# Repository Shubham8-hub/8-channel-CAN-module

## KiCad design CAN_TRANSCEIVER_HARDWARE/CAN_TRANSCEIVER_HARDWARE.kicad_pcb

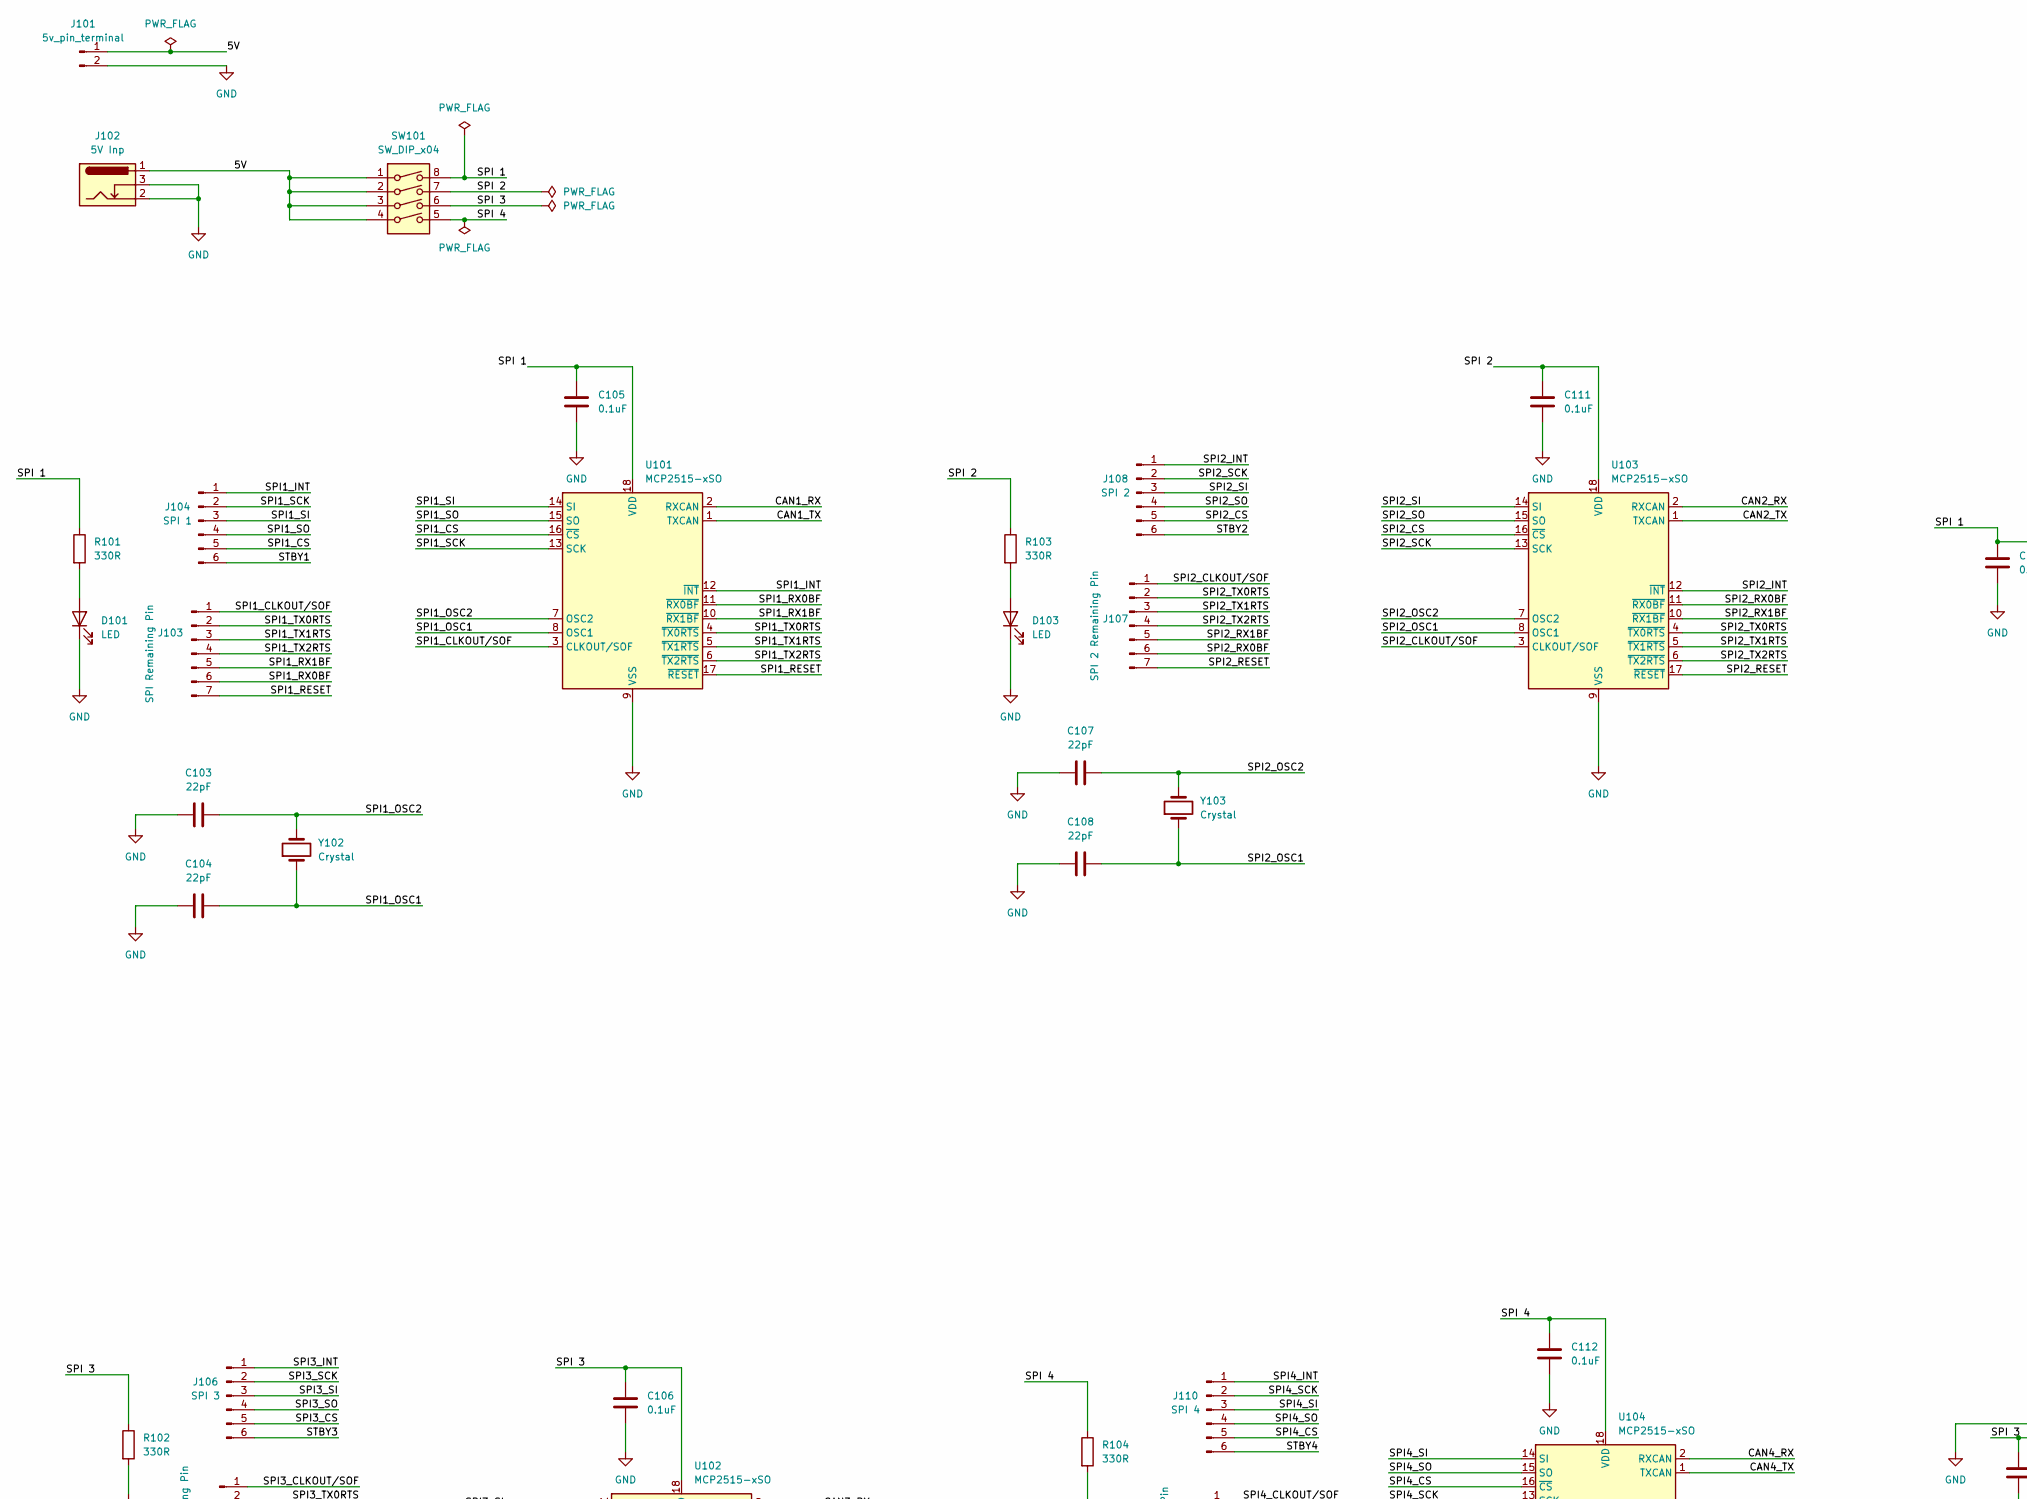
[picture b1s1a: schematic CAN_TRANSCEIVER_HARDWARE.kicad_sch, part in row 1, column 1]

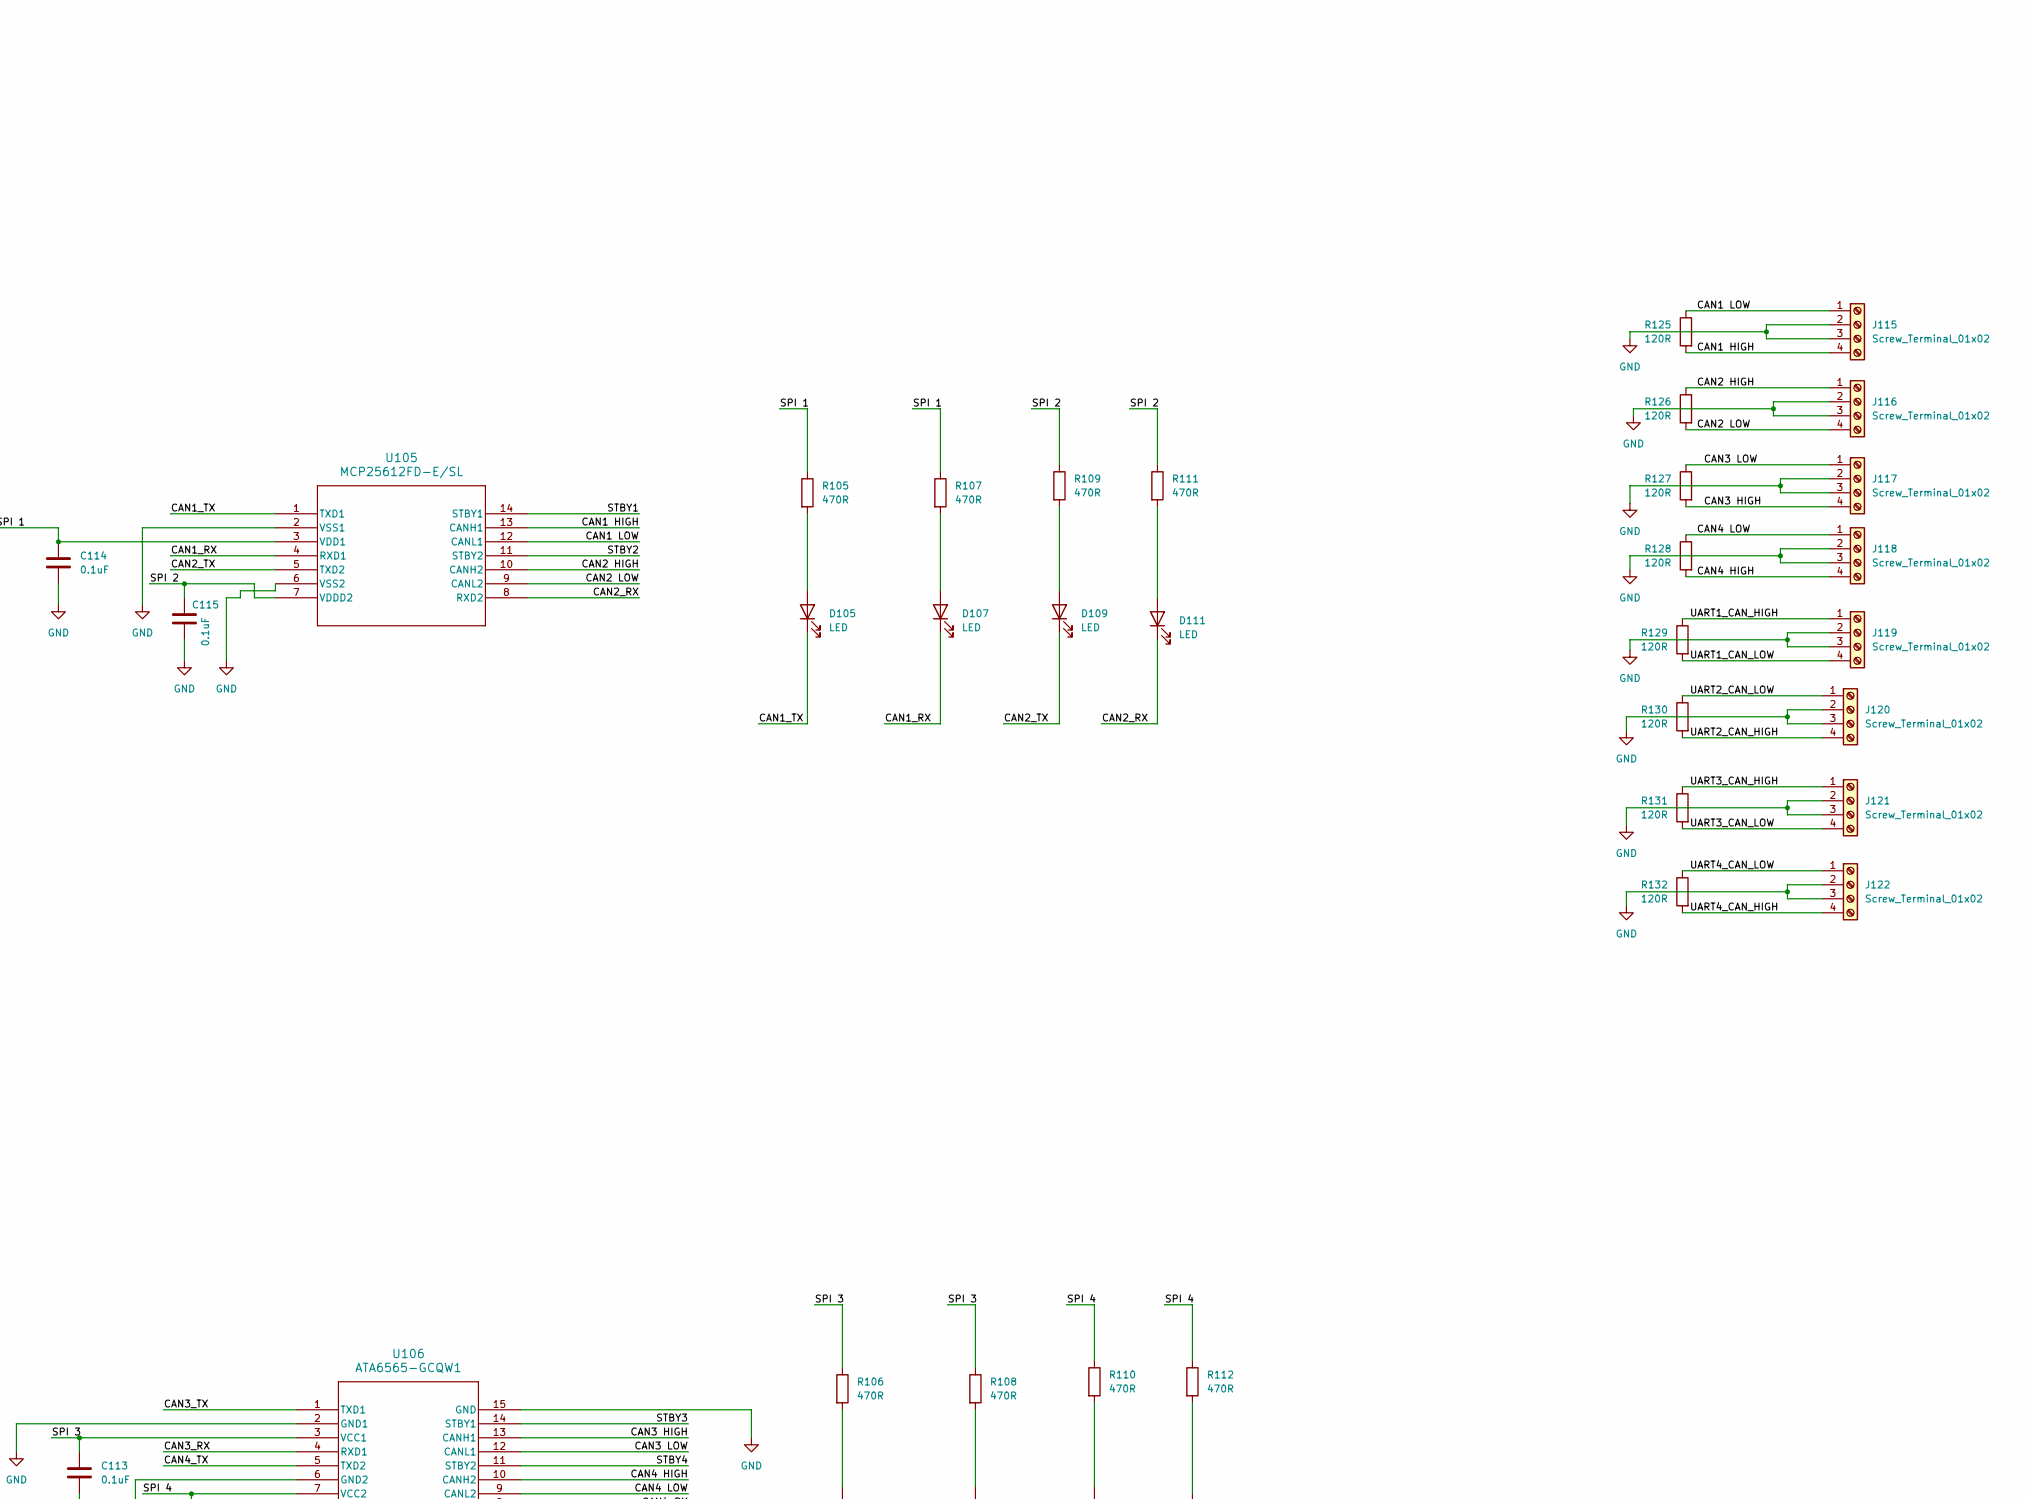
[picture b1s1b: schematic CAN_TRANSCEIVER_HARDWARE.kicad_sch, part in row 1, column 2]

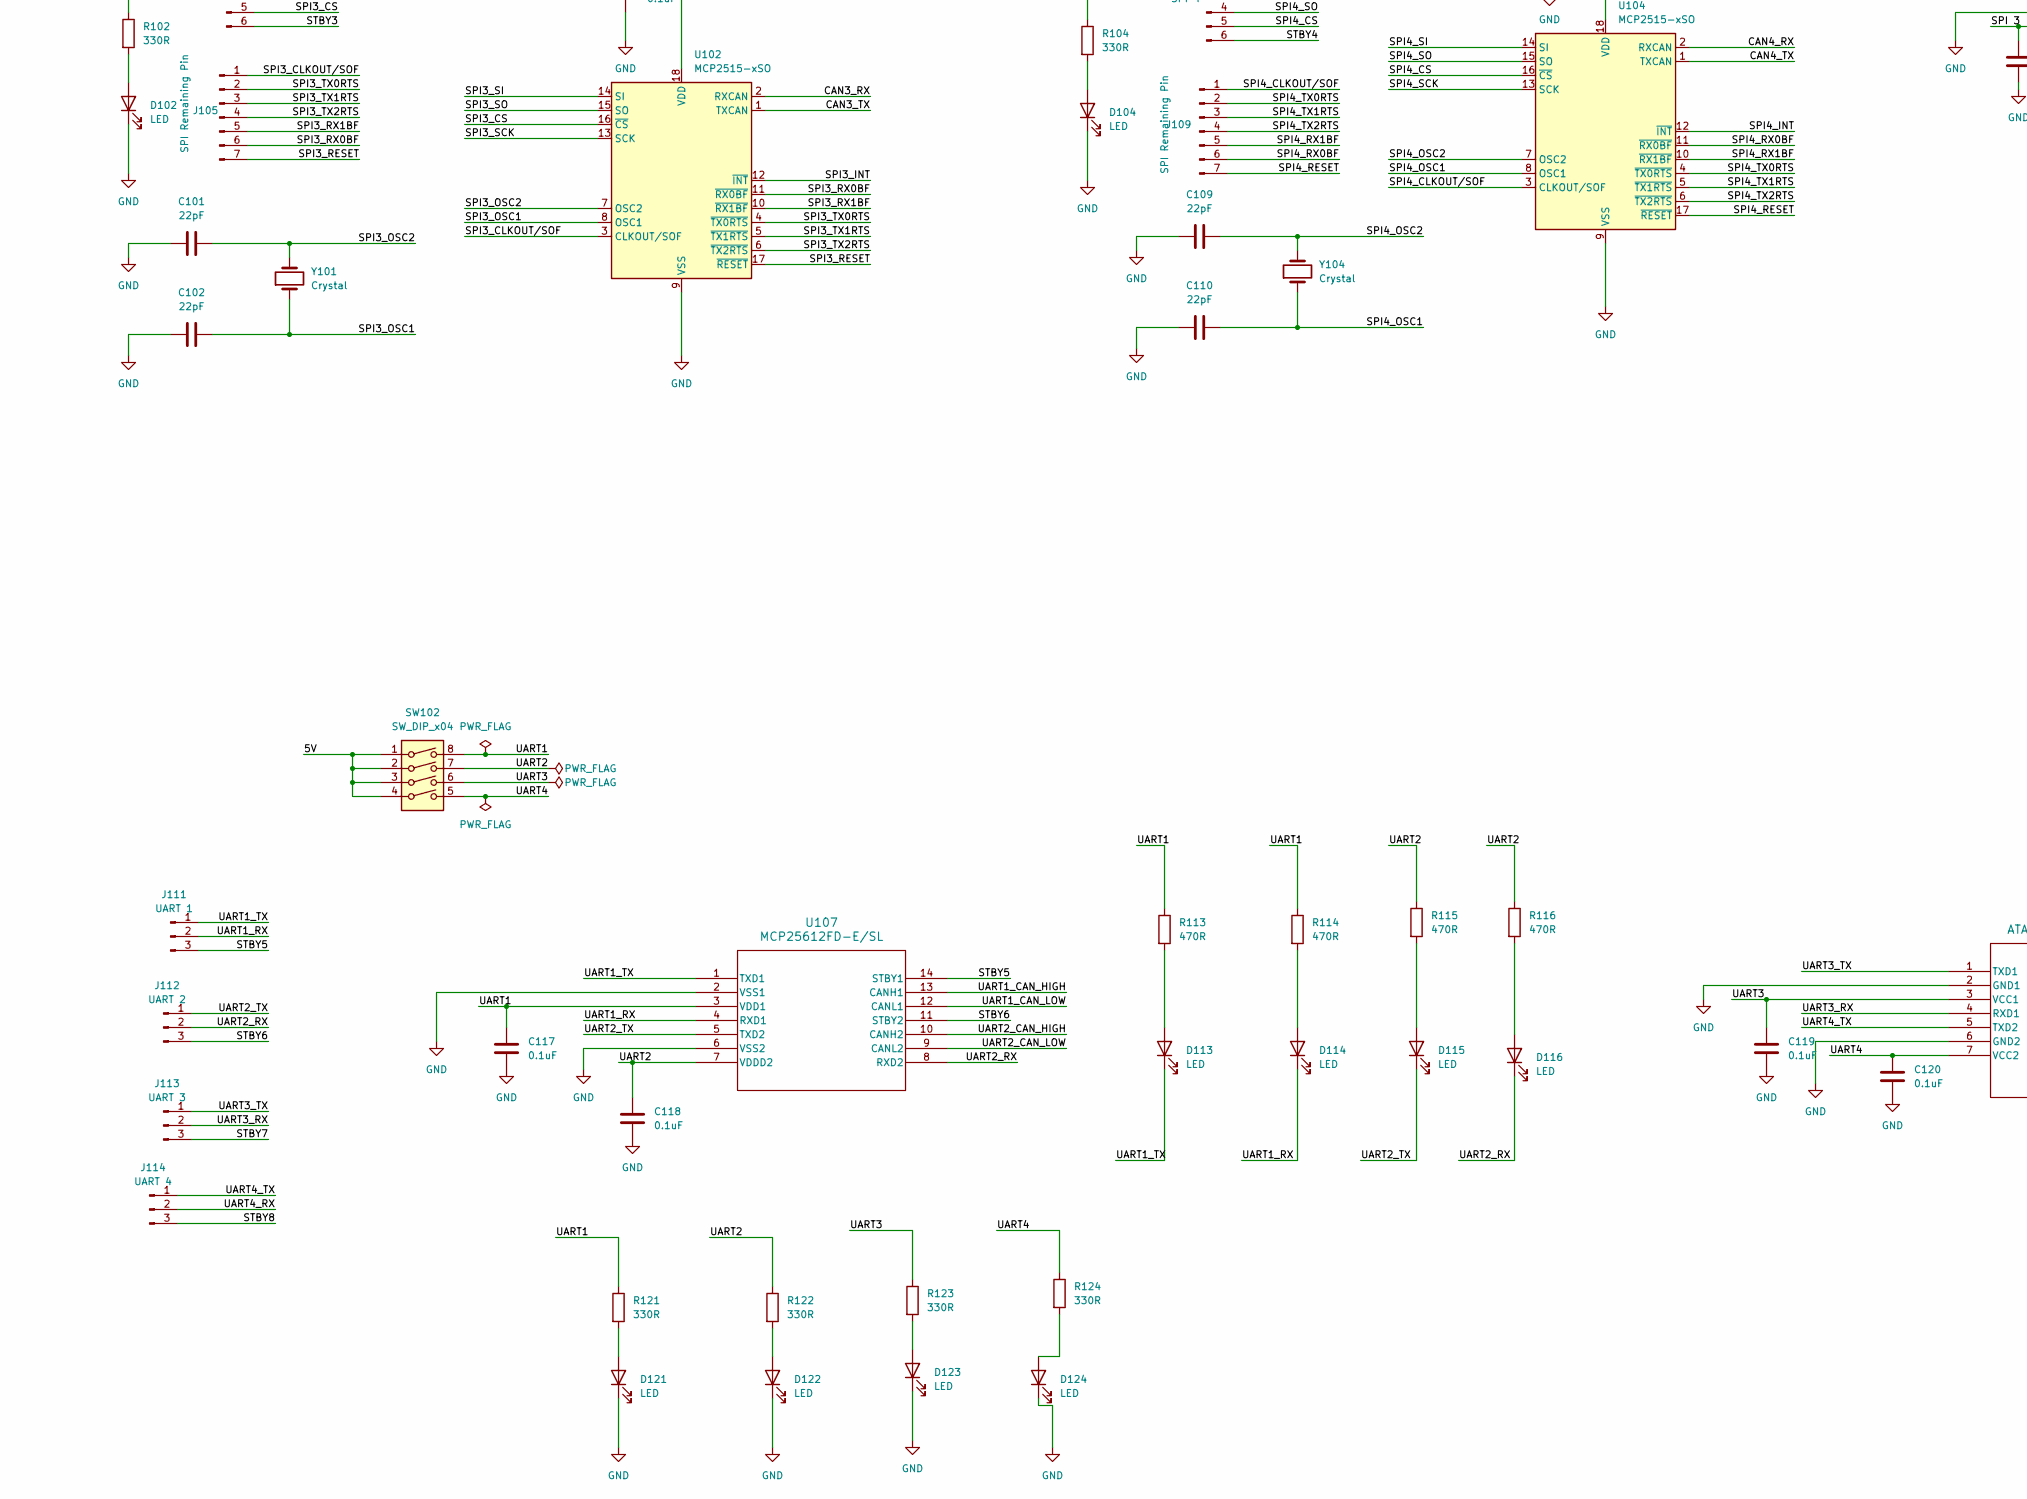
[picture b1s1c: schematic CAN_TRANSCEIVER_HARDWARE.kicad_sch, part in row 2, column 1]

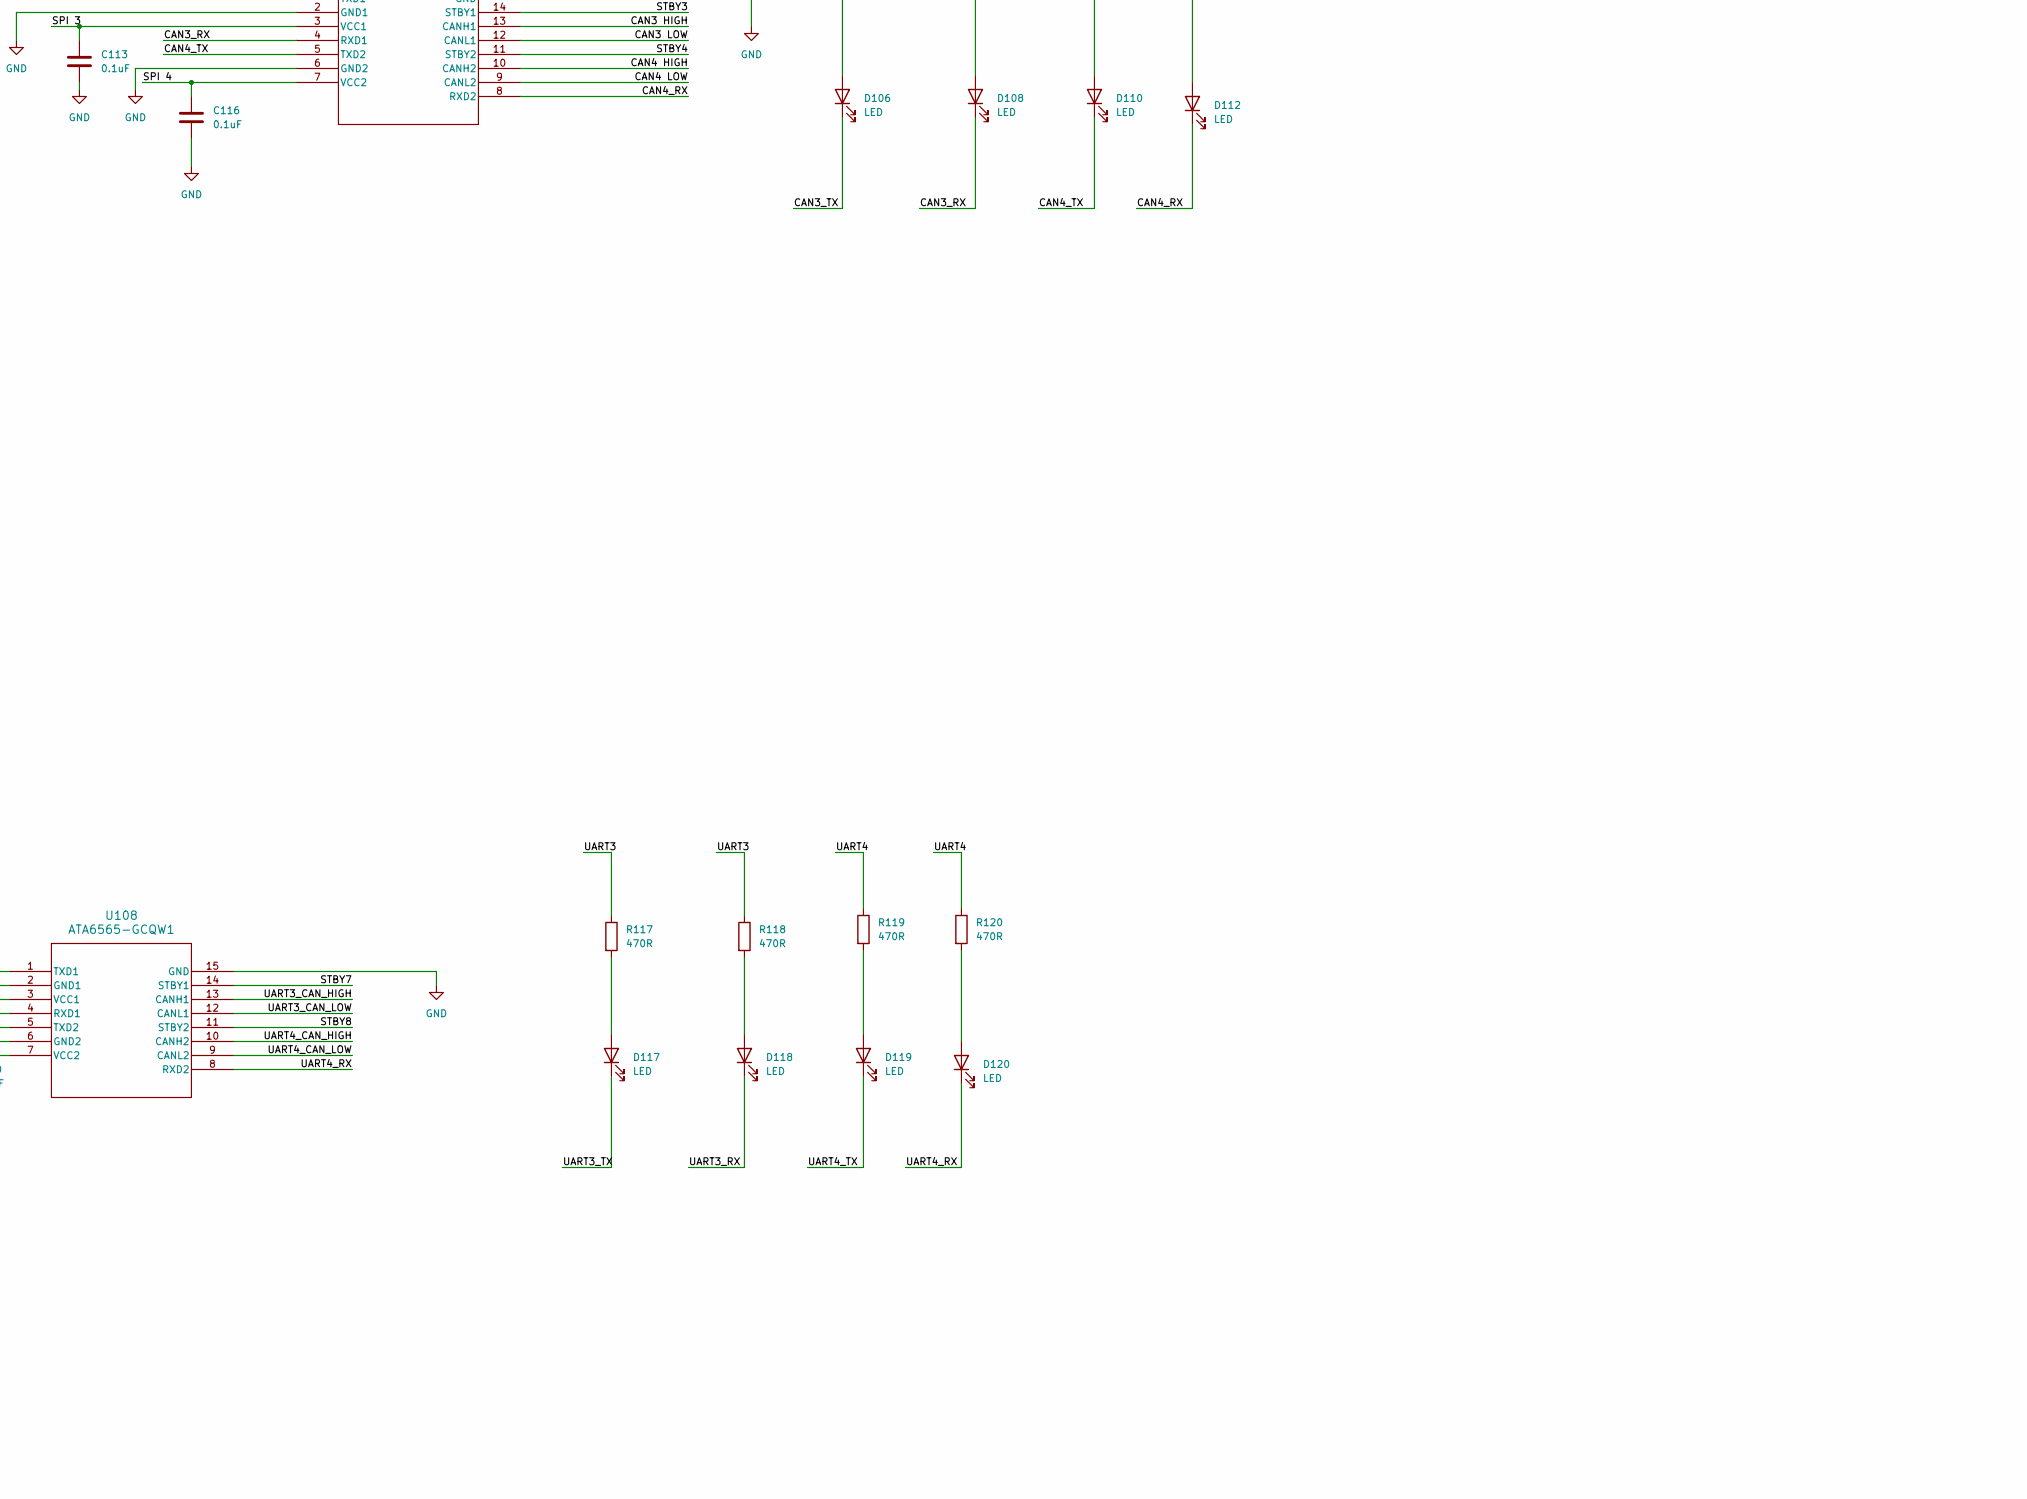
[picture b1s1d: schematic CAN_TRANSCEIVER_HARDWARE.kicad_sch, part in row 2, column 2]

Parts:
C101, C102, C103, C104, C107, C108, C109, C110: 22pF; C_0805_2012Metric_Pad1.18x1.45mm_HandSolder
C105, C106, C111, C112, C113, C114, C115, C116, C117, C118, C119, C120: 0.1uF; C_0805_2012Metric_Pad1.18x1.45mm_HandSolder
D101, D102, D103, D104, D105, D106, D107, D108, D109, D110, D111, D112, D113, D114, D115, D116, D117, D118, D119, D120, D121, D122, D123, D124: LED; LED_1206_3216Metric_Pad1.42x1.75mm_HandSolder
J101: 5v_pin_terminal; PinHeader_1x02_P2.54mm_Vertical
J102: 5V Inp; BarrelJack_Horizontal
J103, J105, J109: SPI Remaining Pin; PinHeader_1x07_P2.54mm_Vertical
J104: SPI 1; PinHeader_1x06_P2.54mm_Vertical
J106: SPI 3; PinHeader_1x06_P2.54mm_Vertical
J107: SPI 2 Remaining Pin; PinHeader_1x07_P2.54mm_Vertical
J108: SPI 2; PinHeader_1x06_P2.54mm_Vertical
J110: SPI 4; PinHeader_1x06_P2.54mm_Vertical
J111: UART 1; PinHeader_1x03_P2.54mm_Vertical
J112: UART 2; PinHeader_1x03_P2.54mm_Vertical
J113: UART 3; PinHeader_1x03_P2.54mm_Vertical
J114: UART 4; PinHeader_1x03_P2.54mm_Vertical
J115, J116, J117, J118, J119, J120, J121, J122: Screw_Terminal_01x02; TerminalBlock_bornier-4_P5.08mm
R101, R102, R103, R104, R121, R122, R123, R124: 330R; R_0805_2012Metric_Pad1.20x1.40mm_HandSolder
R105, R106, R107, R108, R109, R110, R111, R112, R113, R114, R115, R116, R117, R118, R119, R120: 470R; R_0805_2012Metric_Pad1.20x1.40mm_HandSolder
R125, R126, R127, R128, R129, R130, R131, R132: 120R; R_1206_3216Metric_Pad1.30x1.75mm_HandSolder
SW101, SW102: SW_DIP_x04; SW_DIP_SPSTx04_Slide_9.78x12.34mm_W7.62mm_P2.54mm
U101, U102, U103, U104: MCP2515-xSO; MCP2515
U105, U107: MCP25612FD-E/SL; MCP25162FD
U106, U108: ATA6565-GCQW1; VDFN14_QBB_MCH-M
Y101, Y102, Y103, Y104: Crystal; Crystal_HC49-4H_Vertical

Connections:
/5V: J101.1, J102.1, SW101.1, SW101.2, SW101.3, SW101.4, SW102.1, SW102.2, SW102.3, SW102.4
/CAN1 HIGH: J115.4, R125.2, U105.13 (CANH1)
/CAN1 LOW: J115.1, R125.1, U105.12 (CANL1)
/CAN1_RX: D107.1 (K), U101.2 (RXCAN), U105.4 (RXD1)
/CAN1_TX: D105.1 (K), U101.1 (TXCAN), U105.1 (TXD1)
/CAN2 HIGH: J116.1, R126.1, U105.10 (CANH2)
/CAN2 LOW: J116.4, R126.2, U105.9 (CANL2)
/CAN2_RX: D111.1 (K), U103.2 (RXCAN), U105.8 (RXD2)
/CAN2_TX: D109.1 (K), U103.1 (TXCAN), U105.5 (TXD2)
/CAN3 HIGH: J117.4, R127.2, U106.13 (CANH1)
/CAN3 LOW: J117.1, R127.1, U106.12 (CANL1)
/CAN3_RX: D108.1 (K), U102.2 (RXCAN), U106.4 (RXD1)
/CAN3_TX: D106.1 (K), U102.1 (TXCAN), U106.1 (TXD1)
/CAN4 HIGH: J118.4, R128.2, U106.10 (CANH2)
/CAN4 LOW: J118.1, R128.1, U106.9 (CANL2)
/CAN4_RX: D112.1 (K), U104.2 (RXCAN), U106.8 (RXD2)
/CAN4_TX: D110.1 (K), U104.1 (TXCAN), U106.5 (TXD2)
/SPI1_CLKOUT/SOF: J103.1, U101.3 (CLKOUT/SOF)
/SPI1_CS: J104.5, U101.16 (~CS)
/SPI1_INT: J104.1, U101.12 (~INT)
/SPI1_OSC1: C104.2, U101.8 (OSC1), Y102.1
/SPI1_OSC2: C103.2, U101.7 (OSC2), Y102.2
/SPI1_RESET: J103.7, U101.17 (~RESET)
/SPI1_RX0BF: J103.6, U101.11 (~RX0BF)
/SPI1_RX1BF: J103.5, U101.10 (~RX1BF)
/SPI1_SCK: J104.2, U101.13 (SCK)
/SPI1_SI: J104.3, U101.14 (SI)
/SPI1_SO: J104.4, U101.15 (SO)
/SPI1_TX0RTS: J103.2, U101.4 (~TX0RTS)
/SPI1_TX1RTS: J103.3, U101.5 (~TX1RTS)
/SPI1_TX2RTS: J103.4, U101.6 (~TX2RTS)
/SPI2_CLKOUT/SOF: J107.1, U103.3 (CLKOUT/SOF)
/SPI2_CS: J108.5, U103.16 (~CS)
/SPI2_INT: J108.1, U103.12 (~INT)
/SPI2_OSC1: C108.2, U103.8 (OSC1), Y103.1
/SPI2_OSC2: C107.2, U103.7 (OSC2), Y103.2
/SPI2_RESET: J107.7, U103.17 (~RESET)
/SPI2_RX0BF: J107.6, U103.11 (~RX0BF)
/SPI2_RX1BF: J107.5, U103.10 (~RX1BF)
/SPI2_SCK: J108.2, U103.13 (SCK)
/SPI2_SI: J108.3, U103.14 (SI)
/SPI2_SO: J108.4, U103.15 (SO)
/SPI2_TX0RTS: J107.2, U103.4 (~TX0RTS)
/SPI2_TX1RTS: J107.3, U103.5 (~TX1RTS)
/SPI2_TX2RTS: J107.4, U103.6 (~TX2RTS)
/SPI3_CLKOUT/SOF: J105.1, U102.3 (CLKOUT/SOF)
/SPI3_CS: J106.5, U102.16 (~CS)
/SPI3_INT: J106.1, U102.12 (~INT)
/SPI3_OSC1: C102.2, U102.8 (OSC1), Y101.1
/SPI3_OSC2: C101.2, U102.7 (OSC2), Y101.2
/SPI3_RESET: J105.7, U102.17 (~RESET)
/SPI3_RX0BF: J105.6, U102.11 (~RX0BF)
/SPI3_RX1BF: J105.5, U102.10 (~RX1BF)
/SPI3_SCK: J106.2, U102.13 (SCK)
/SPI3_SI: J106.3, U102.14 (SI)
/SPI3_SO: J106.4, U102.15 (SO)
/SPI3_TX0RTS: J105.2, U102.4 (~TX0RTS)
/SPI3_TX1RTS: J105.3, U102.5 (~TX1RTS)
/SPI3_TX2RTS: J105.4, U102.6 (~TX2RTS)
/SPI4_CLKOUT/SOF: J109.1, U104.3 (CLKOUT/SOF)
/SPI4_CS: J110.5, U104.16 (~CS)
/SPI4_INT: J110.1, U104.12 (~INT)
/SPI4_OSC1: C110.2, U104.8 (OSC1), Y104.1
/SPI4_OSC2: C109.2, U104.7 (OSC2), Y104.2
/SPI4_RESET: J109.7, U104.17 (~RESET)
/SPI4_RX0BF: J109.6, U104.11 (~RX0BF)
/SPI4_RX1BF: J109.5, U104.10 (~RX1BF)
/SPI4_SCK: J110.2, U104.13 (SCK)
/SPI4_SI: J110.3, U104.14 (SI)
/SPI4_SO: J110.4, U104.15 (SO)
/SPI4_TX0RTS: J109.2, U104.4 (~TX0RTS)
/SPI4_TX1RTS: J109.3, U104.5 (~TX1RTS)
/SPI4_TX2RTS: J109.4, U104.6 (~TX2RTS)
/SPI 1: C105.1, C114.1, R101.1, R105.1, R107.1, SW101.8, U101.18 (VDD), U105.3 (VDD1)
/SPI 2: C111.1, C115.1, R103.1, R109.1, R111.1, SW101.7, U103.18 (VDD), U105.7 (VDDD2)
/SPI 3: C106.1, C113.1, R102.1, R106.1, R108.1, SW101.6, U102.18 (VDD), U106.3 (VCC1)
/SPI 4: C112.1, C116.1, R104.1, R110.1, R112.1, SW101.5, U104.18 (VDD), U106.7 (VCC2)
/STBY1: J104.6, U105.14 (STBY1)
/STBY2: J108.6, U105.11 (STBY2)
/STBY3: J106.6, U106.14 (STBY1)
/STBY4: J110.6, U106.11 (STBY2)
/STBY5: J111.3, U107.14 (STBY1)
/STBY6: J112.3, U107.11 (STBY2)
/STBY7: J113.3, U108.14 (STBY1)
/STBY8: J114.3, U108.11 (STBY2)
/UART1: C117.1, R113.1, R114.1, R121.1, SW102.8, U107.3 (VDD1)
/UART1_CAN_HIGH: J119.1, R129.1, U107.13 (CANH1)
/UART1_CAN_LOW: J119.4, R129.2, U107.12 (CANL1)
/UART1_RX: D114.1 (K), J111.2, U107.4 (RXD1)
/UART1_TX: D113.1 (K), J111.1, U107.1 (TXD1)
/UART2: C118.1, R115.1, R116.1, R122.1, SW102.7, U107.7 (VDDD2)
/UART2_CAN_HIGH: J120.4, R130.2, U107.10 (CANH2)
/UART2_CAN_LOW: J120.1, R130.1, U107.9 (CANL2)
/UART2_RX: D116.1 (K), J112.2, U107.8 (RXD2)
/UART2_TX: D115.1 (K), J112.1, U107.5 (TXD2)
/UART3: C119.1, R117.1, R118.1, R123.1, SW102.6, U108.3 (VCC1)
/UART3_CAN_HIGH: J121.1, R131.1, U108.13 (CANH1)
/UART3_CAN_LOW: J121.4, R131.2, U108.12 (CANL1)
/UART3_RX: D118.1 (K), J113.2, U108.4 (RXD1)
/UART3_TX: D117.1 (K), J113.1, U108.1 (TXD1)
/UART4: C120.1, R119.1, R120.1, R124.1, SW102.5, U108.7 (VCC2)
/UART4_CAN_HIGH: J122.4, R132.2, U108.10 (CANH2)
/UART4_CAN_LOW: J122.1, R132.1, U108.9 (CANL2)
/UART4_RX: D120.1 (K), J114.2, U108.8 (RXD2)
/UART4_TX: D119.1 (K), J114.1, U108.5 (TXD2)
GND: C101.1, C102.1, C103.1, C104.1, C105.2, C106.2, C107.1, C108.1, C109.1, C110.1, C111.2, C112.2, C113.2, C114.2, C115.2, C116.2, C117.2, C118.2, C119.2, C120.2, D101.1 (K), D102.1 (K), D103.1 (K), D104.1 (K), D121.1 (K), D122.1 (K), D123.1 (K), D124.1 (K), J101.2, J102.2, J102.3, J115.2, J115.3, J116.2, J116.3, J117.2, J117.3, J118.2, J118.3, J119.2, J119.3, J120.2, J120.3, J121.2, J121.3, J122.2, J122.3, U101.9 (VSS), U102.9 (VSS), U103.9 (VSS), U104.9 (VSS), U105.2 (VSS1), U105.6 (VSS2), U106.2 (GND1), U106.6 (GND2), U106.15 (GND), U107.2 (VSS1), U107.6 (VSS2), U108.2 (GND1), U108.6 (GND2), U108.15 (GND)
unnamed: D101.2 (A), R101.2
unnamed: D102.2 (A), R102.2
unnamed: D103.2 (A), R103.2
unnamed: D104.2 (A), R104.2
unnamed: D105.2 (A), R105.2
unnamed: D106.2 (A), R106.2
unnamed: D107.2 (A), R107.2
unnamed: D108.2 (A), R108.2
unnamed: D109.2 (A), R109.2
unnamed: D110.2 (A), R110.2
unnamed: D111.2 (A), R111.2
unnamed: D112.2 (A), R112.2
unnamed: D113.2 (A), R113.2
unnamed: D114.2 (A), R114.2
unnamed: D115.2 (A), R115.2
unnamed: D116.2 (A), R116.2
unnamed: D117.2 (A), R117.2
unnamed: D118.2 (A), R118.2
unnamed: D119.2 (A), R119.2
unnamed: D120.2 (A), R120.2
unnamed: D121.2 (A), R121.2
unnamed: D122.2 (A), R122.2
unnamed: D123.2 (A), R123.2
unnamed: D124.2 (A), R124.2

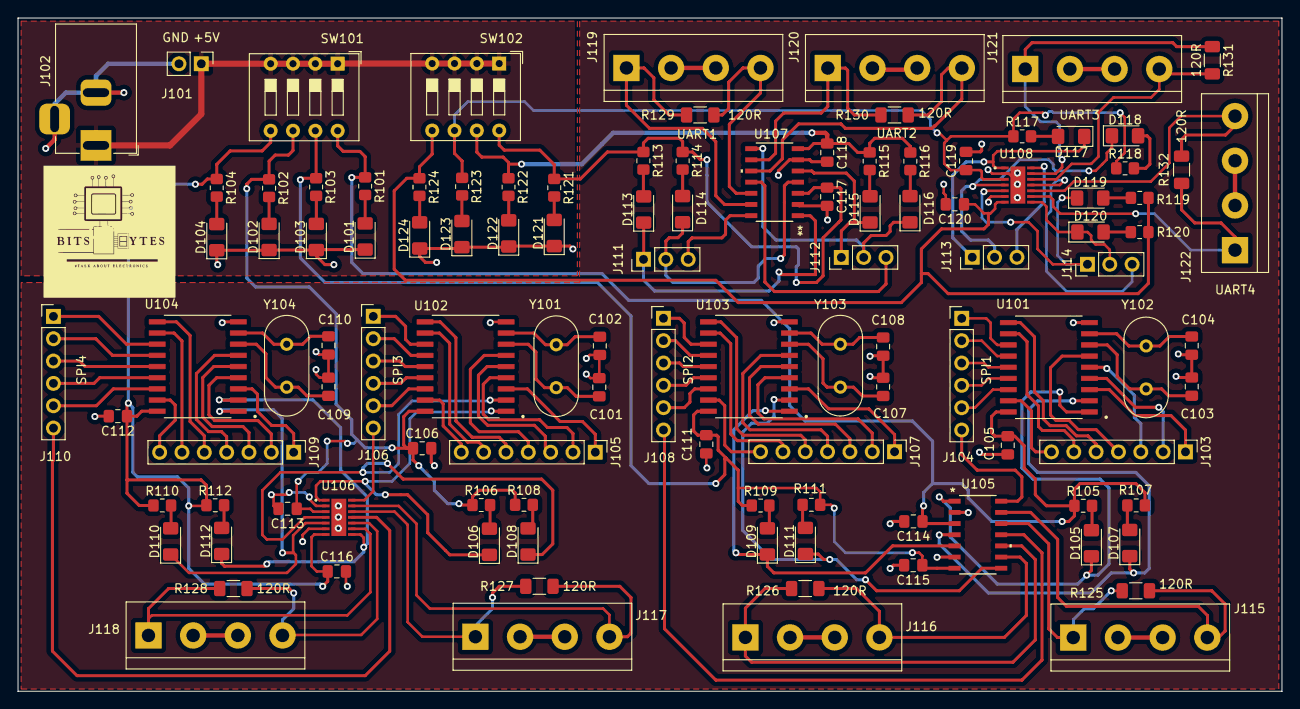
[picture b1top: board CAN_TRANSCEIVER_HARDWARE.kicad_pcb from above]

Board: 2 copper layers, 143.7 x 76.6 mm, 112 parts (0 on the bottom side), 130 nets.

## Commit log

2024-01-10 gitignore file
2024-01-10 Custom Footprint
2024-01-10 Datasheeet and refernce design
2024-01-10 Schematic files
2024-01-10 Hardware design files
2024-01-11 Added logo in the PCB and added stackup table
2024-01-11 updated git ignore file
2024-01-11 BOM files
2024-01-11 ibom file
2024-01-11 Remaining files
2024-01-11 deleted files
